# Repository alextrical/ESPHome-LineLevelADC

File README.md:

# Line Level Audio ADC ESP32 devkit for ESPHome

ESPHome + ESP32-based Audio ADC with line level analog input for music streaming to local network using WiFi.

Simple goal is to provide proof-of-concept development hardware for ESPHome and Music Assistant developers.

Example use-case and flow-chart:

* Turntable LP-Player -> Preamplifier -> ESP32 with I2S line level ADC -> WiFi -> Music Assistant -> Speakers

What this would basically achieve is a network-attached stereo sound capture device for analogue HiFi sources.

Note! Developer help wanted with ESPHome Audio ADC drivers and pipeline for streaming to Music Assistant.

Current draft prototype is schematic PCB design in KiCad of development board with header for an ADC module.

This early draft is designed to use ESP32-S3 and PCM1808 modules together to enable a 3.5mm jack for input.

Related community discussions:
- https://github.com/orgs/music-assistant/discussions/3763
- https://github.com/orgs/FutureProofHomes/discussions/21
- https://github.com/orgs/music-assistant/discussions/2343

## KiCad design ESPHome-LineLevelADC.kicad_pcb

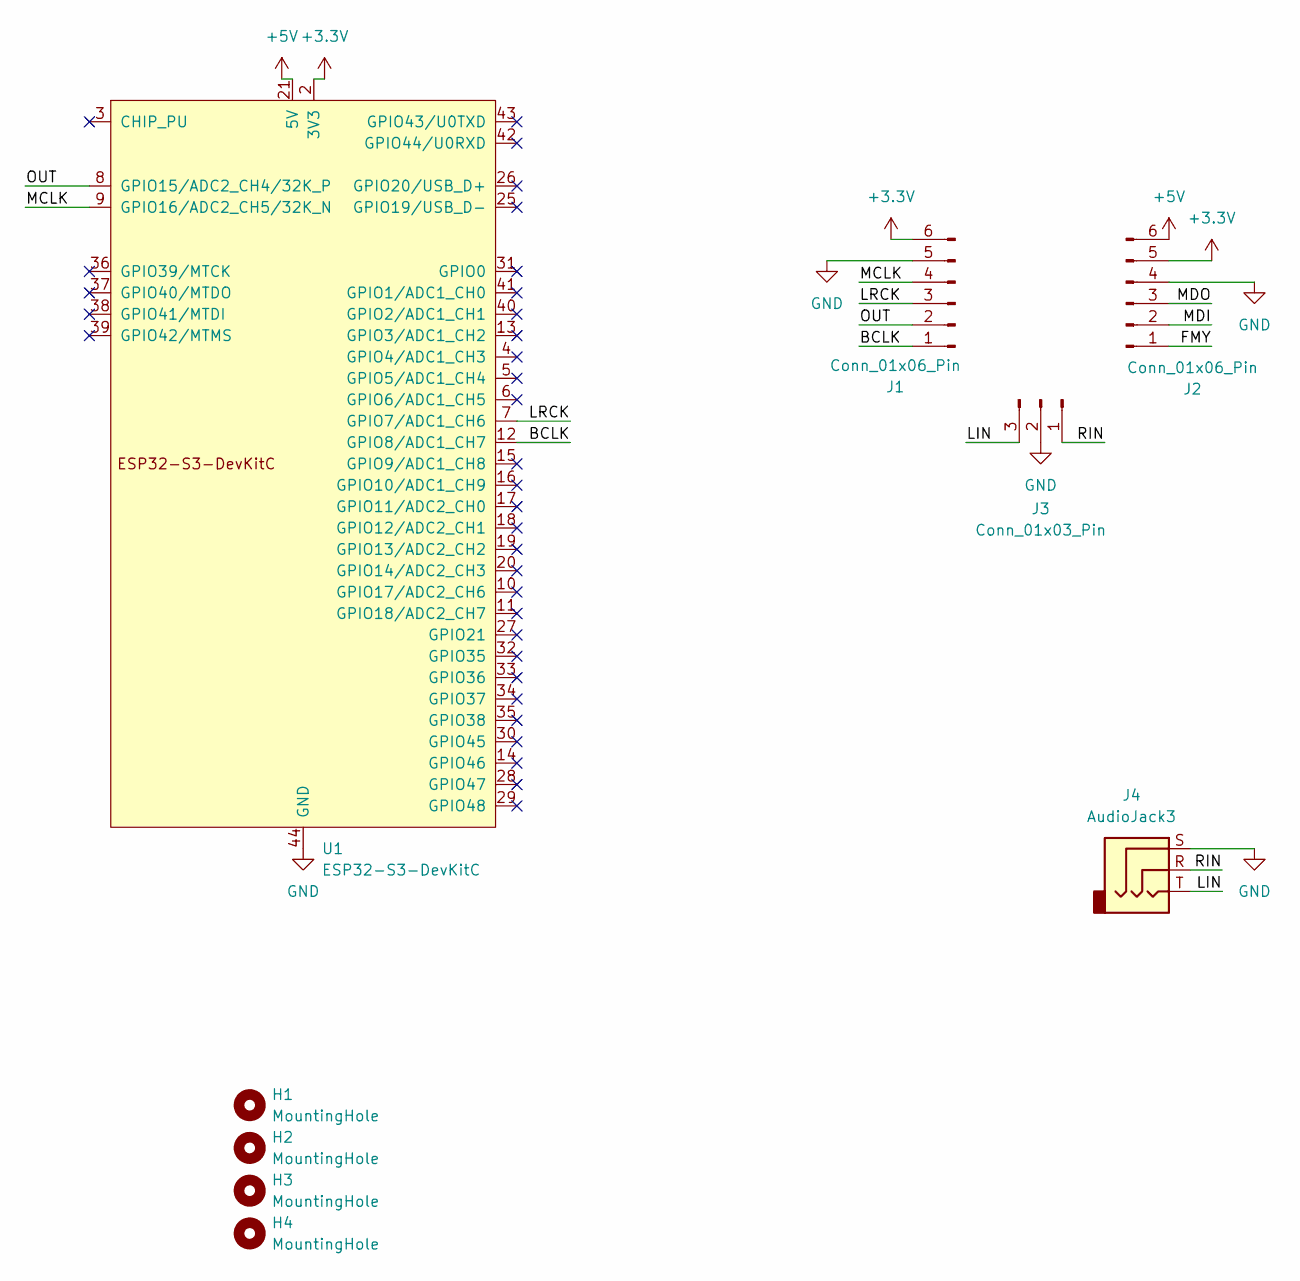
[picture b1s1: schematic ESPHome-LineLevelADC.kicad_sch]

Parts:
H1, H2, H3, H4: MountingHole; MountingHole_3.2mm_M3
J1, J2: Conn_01x06_Pin; PinHeader_1x06_P2.54mm_Vertical
J3: Conn_01x03_Pin; PinSocket_1x03_P2.54mm_Vertical
J4: AudioJack3; Jack_3.5mm_CUI_SJ1-3523N_Horizontal
U1: ESP32-S3-DevKitC

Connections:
+3.3V: J1.6, J2.5, U1.1 (3V3), U1.2 (3V3)
+5V: J2.6, U1.21 (5V)
/BCLK: J1.1, U1.12 (GPIO8/ADC1_CH7)
/FMY: J2.1
/LIN: J3.3, J4.T
/LRCK: J1.3, U1.7 (GPIO7/ADC1_CH6)
/MCLK: J1.4, U1.9 (GPIO16/ADC2_CH5/32K_N)
/MDI: J2.2
/MDO: J2.3
/OUT: J1.2, U1.8 (GPIO15/ADC2_CH4/32K_P)
/RIN: J3.1, J4.R
GND: J1.5, J2.4, J3.2, J4.S, U1.22 (GND), U1.23 (GND), U1.24 (GND), U1.44 (GND)

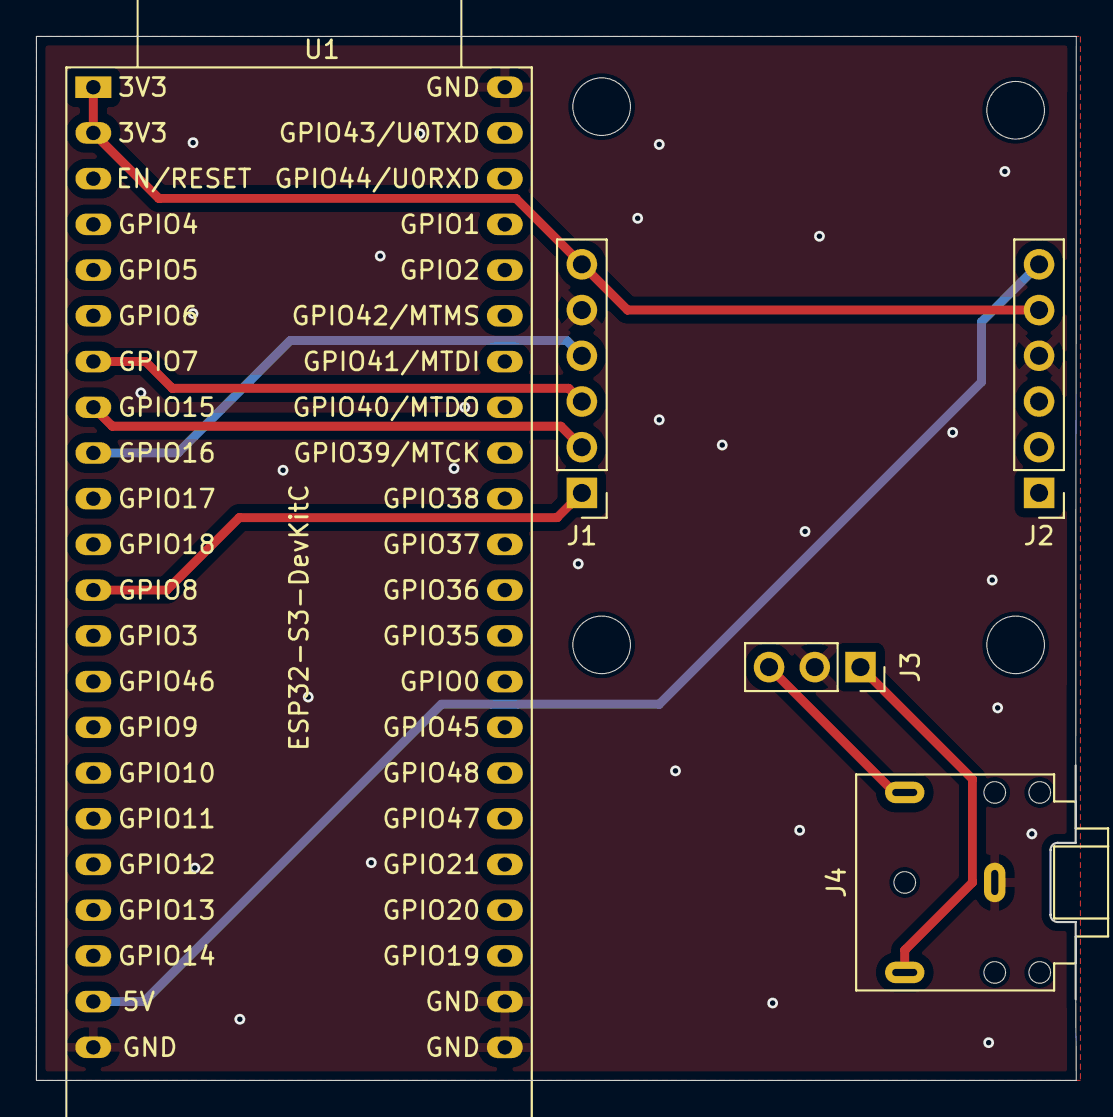
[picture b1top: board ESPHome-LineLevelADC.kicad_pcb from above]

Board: 2 copper layers, 57.7 x 57.9 mm, 9 parts (0 on the bottom side), 9 nets.

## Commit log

2025-03-22 Remove cache files that shouldn't be in Repo
